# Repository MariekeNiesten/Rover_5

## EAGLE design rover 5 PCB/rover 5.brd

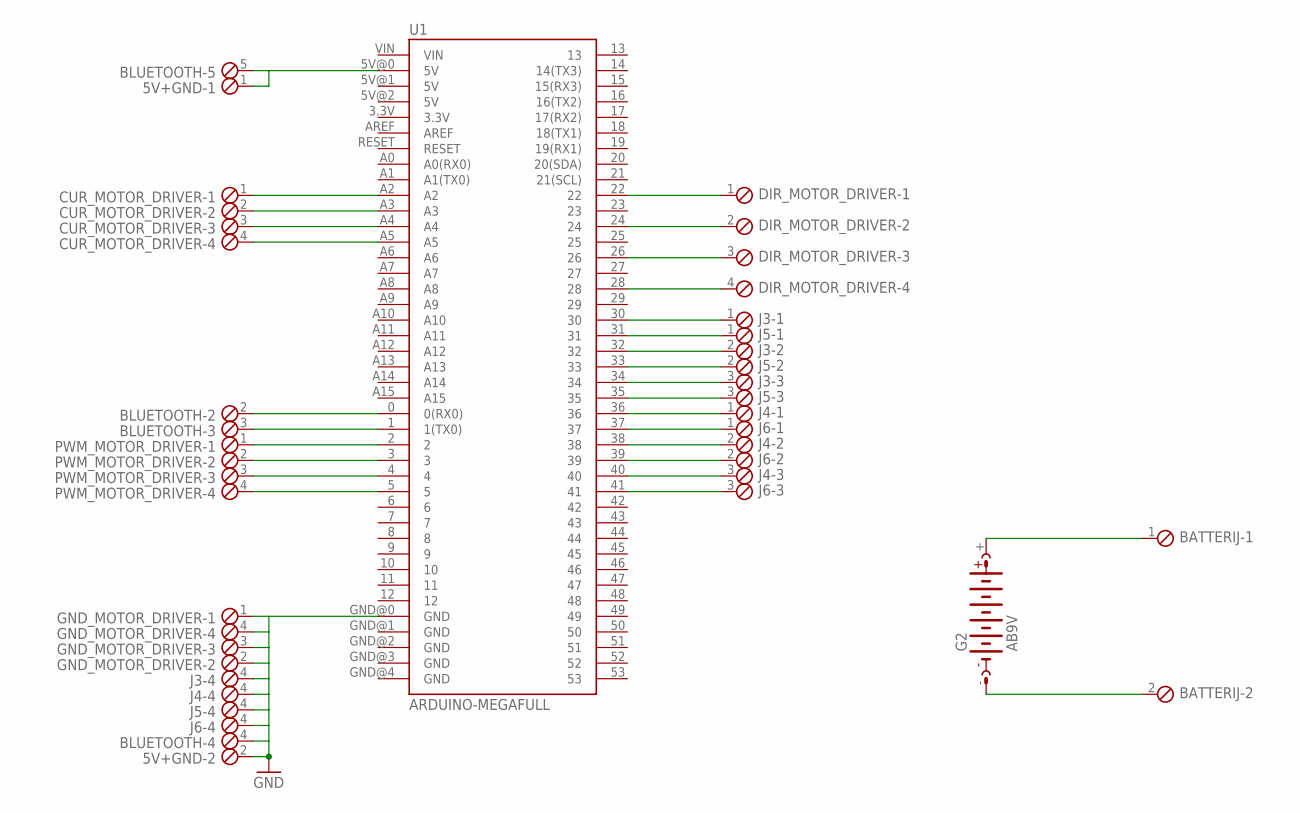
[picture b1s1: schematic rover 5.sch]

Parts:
5V+GND: MPT2; 2POL254
BATTERIJ: MPT2; 2POL254
BLUETOOTH: MPT6; 6POL254
CUR_MOTOR_DRIVER: MPT4; 4POL254
DIR_MOTOR_DRIVER: MPT4; 4POL254
G2: AB9V
GND_MOTOR_DRIVER: MPT4; 4POL254
J3, J4, J5, J6: MPT4; 4POL254
PWM_MOTOR_DRIVER: MPT4; 4POL254
U1: ARDUINO-MEGAFULL; ARDUINO_MEGA

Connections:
GND: 5V+GND.2, BLUETOOTH.4, GND_MOTOR_DRIVER.1, GND_MOTOR_DRIVER.2, GND_MOTOR_DRIVER.3, GND_MOTOR_DRIVER.4, J3.4, J4.4, J5.4, J6.4, U1.GND@0 (GND)
unnamed: DIR_MOTOR_DRIVER.1, U1.22
unnamed: PWM_MOTOR_DRIVER.1, U1.2
unnamed: PWM_MOTOR_DRIVER.2, U1.3
unnamed: PWM_MOTOR_DRIVER.3, U1.4
unnamed: PWM_MOTOR_DRIVER.4, U1.5
unnamed: DIR_MOTOR_DRIVER.2, U1.24
unnamed: DIR_MOTOR_DRIVER.3, U1.26
unnamed: DIR_MOTOR_DRIVER.4, U1.28
unnamed: J3.1, U1.30
unnamed: CUR_MOTOR_DRIVER.1, U1.A2
unnamed: CUR_MOTOR_DRIVER.2, U1.A3
unnamed: CUR_MOTOR_DRIVER.3, U1.A4
unnamed: CUR_MOTOR_DRIVER.4, U1.A5
unnamed: J5.1, U1.31
unnamed: J3.2, U1.32
unnamed: J5.2, U1.33
unnamed: J3.3, U1.34
unnamed: J5.3, U1.35
unnamed: J4.1, U1.36
unnamed: J6.1, U1.37
unnamed: J4.2, U1.38
unnamed: J6.2, U1.39
unnamed: J4.3, U1.40
unnamed: J6.3, U1.41
unnamed: BLUETOOTH.2, U1.0 (0(RX0))
unnamed: BLUETOOTH.3, U1.1 (1(TX0))
unnamed: 5V+GND.1, BLUETOOTH.5, U1.5V@0 (5V)
unnamed: BATTERIJ.1, G2.+
unnamed: BATTERIJ.2, G2.-

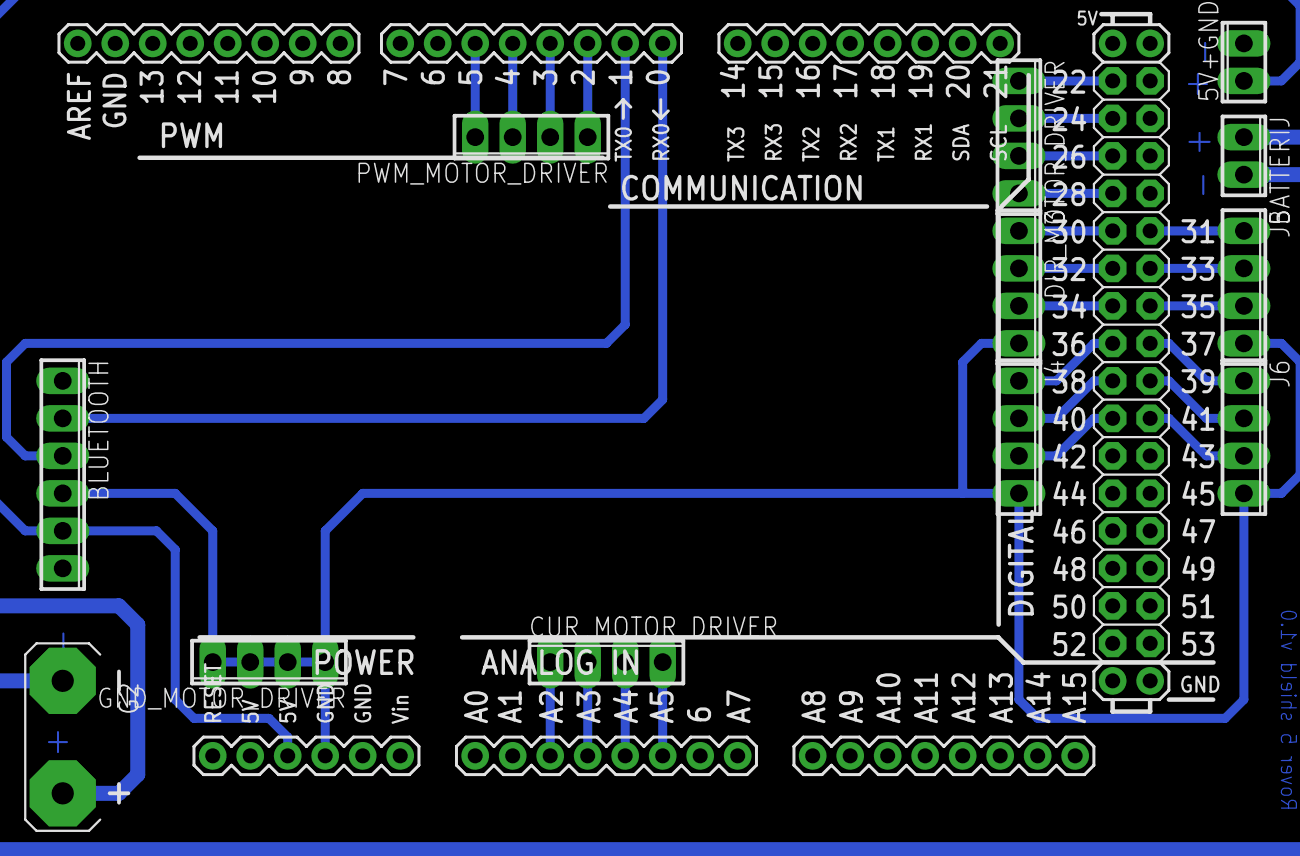
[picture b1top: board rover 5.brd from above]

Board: 2 copper layers, 13 parts (0 on the bottom side), 30 nets.

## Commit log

2015-05-27 :circus_tent: Added .gitattributes & .gitignore files
2015-05-27 De Rover 5 files
2015-05-27 Create Youtubelinkfilmpje

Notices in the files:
parts and their libraries:
SparkFun-Boards: Licensing: Creative Commons ShareAlike 4.0 International - https://creativecommons.org/licenses/by-sa/4.0
